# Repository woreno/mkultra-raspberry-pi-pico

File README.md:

# mkultra-raspberry-pi-pico
A stereo audio recorder and ultrasound player using Raspberry Pi Pico made in 2022

I have severe tinitus running my ears, sometimes suddenly i feel my ears popping. For fun i decided to make a device to record my ears. So this consists of a SD Card reader, a small display, piezo speaker, a set of buttons, a dial (rotary encoder), two small electrec microphones, a op-amp circuit for amplification, and a Raspberry Pi Pico to record the sound. After i added a ultrasonic speaker to sweep frequencies. The Raspberry Pi Pico gadget and the microphone amplifier goes into 2 separated boxes. The microphone amplifier can be disconnected from Raspberry Pi Pico box, and connected to a PC line jack for recording audio using the PC software instead.

The small electrec microphones (cushioned) enters one's ears, and goes to microphone amplifier box then to the Raspberry Pi Pico box where the user can control the recording. There's also an option that draws the microphone levels on screen, so the microphones gain can be ajusted thru the potentiometers inside the amplifier box conveniently. 

While recording, the user can save into a file timestamps generated when a button is pressed. In this way the user can take note when some strange tinitus sound appears by just pressing a button, and review later these timestamps along the recorded file.

The system uses fat filesystem, Pico DMA's ADC channels, two cores, and for performance reasons, it records fat clusters sequentially and writes the fat once the records ends, so the SDCard shall only have files created by this system. The sound is recorded stereo with a 12-bit amplitude quantization due to the Raspberry Pi Pico ADC limits, and the rate (samples per second) can be selected from the user interface. From the main menu user can put the ultrasonic speaker playing, sweeping frequencies with the dial (in this setup i used a cheap ultrasonic speaker (2.5€), capable of 36KHz so just a bit above the human ear limit, 20 kHz. 

**About the results**
There was a constant beat probably coming from heart beats, the recording **test.wav**, after noise reduction, and equalizer, feels very ghostly.

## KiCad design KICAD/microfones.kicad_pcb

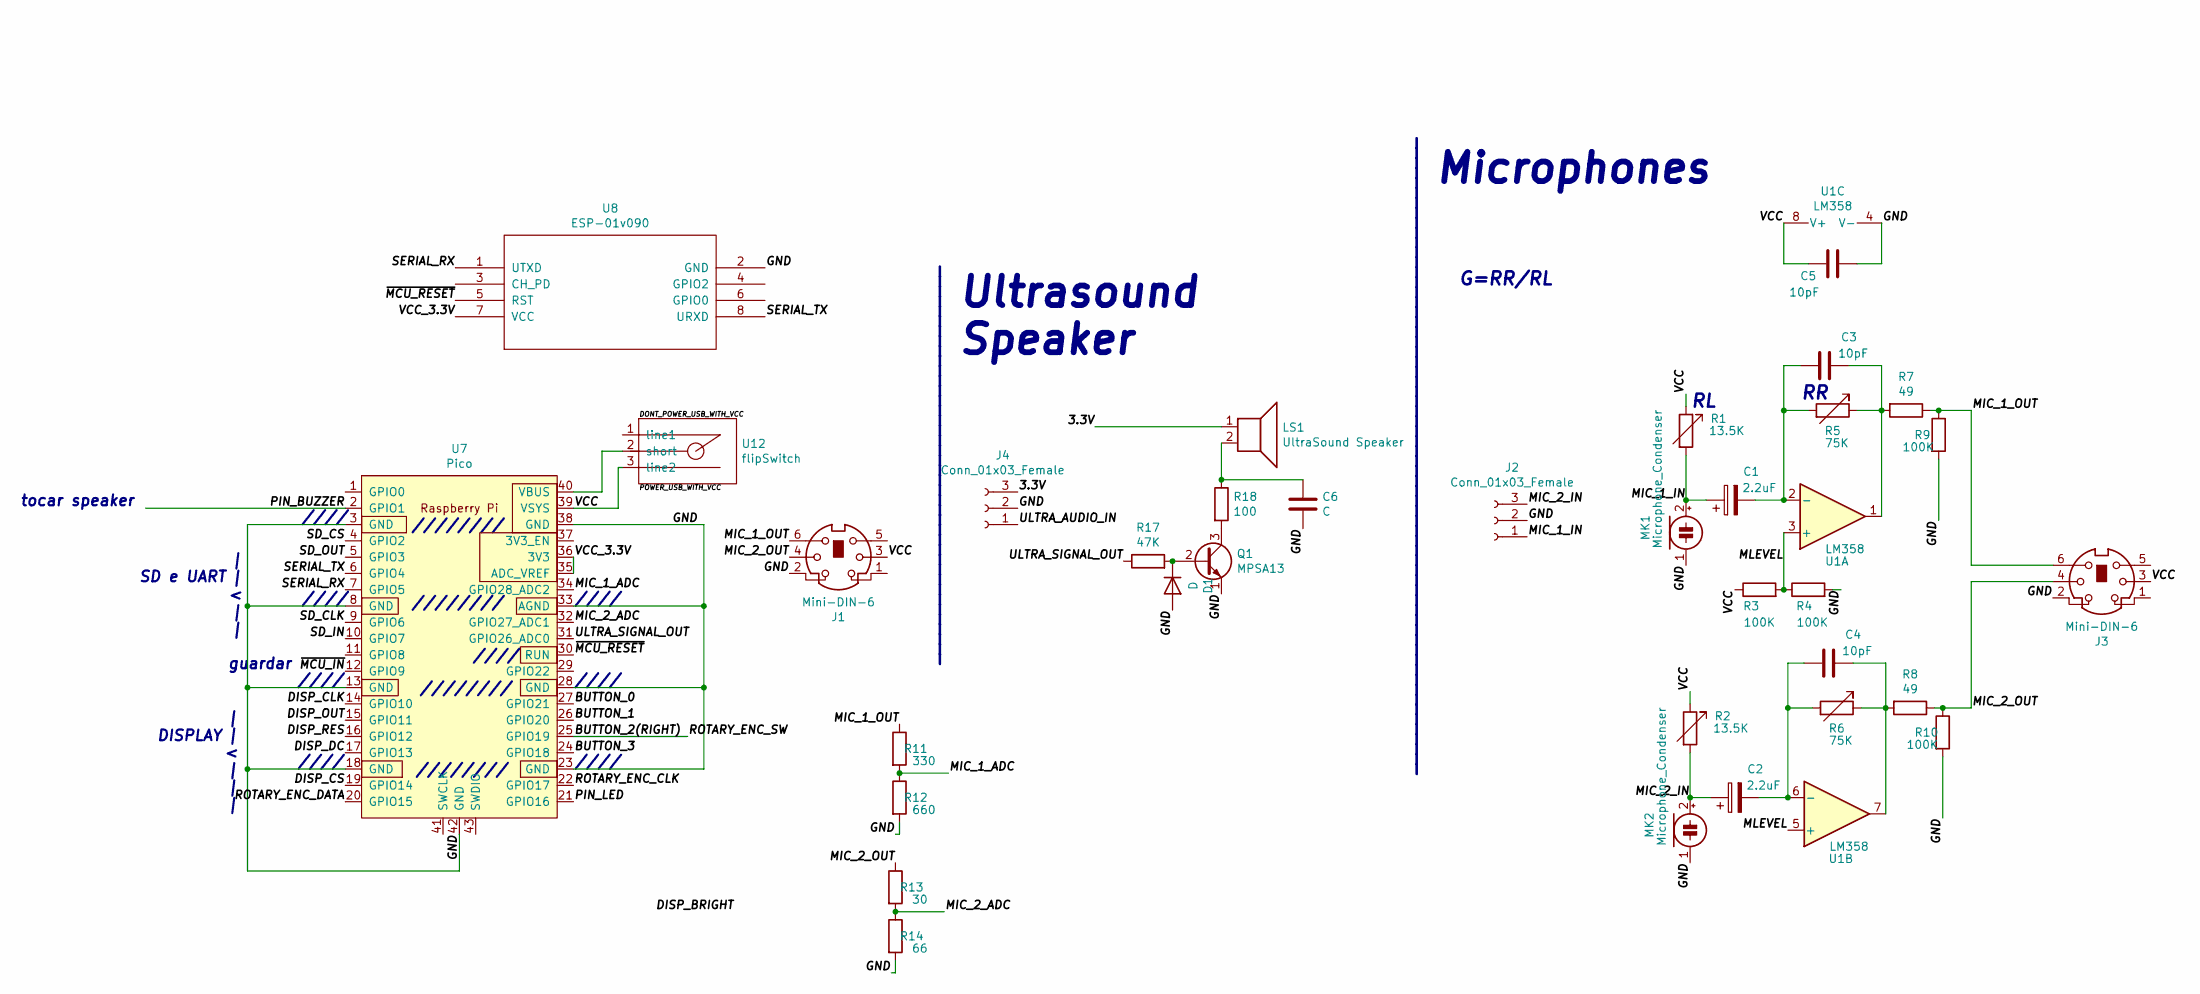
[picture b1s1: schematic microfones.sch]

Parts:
C1, C2: 2.2uF; standard_2pins
C3, C4, C5: 10pF; standard_2pins_half
C6: C; standard_2pins_half
D1: D; standard_2pins
J1, J3: Mini-DIN-6; minidin5
J2, J4: Conn_01x03_Female; PinHeader_1x03_P1.00mm_Horizontal
LS1: UltraSound Speaker; standard_2pins
MK1, MK2: Microphone_Condenser; standard_2pins
Q1: MPSA13; TO-92_Inline
R1, R2: 13.5K; standard_2pins
R3, R4, R9, R10: 100K; standard_2pins
R5, R6: 75K; standard_2pins
R7, R8: 49; standard_2pins
R11: 330; standard_2pins
R12: 660; standard_2pins
R13: 30; standard_2pins
R14: 66; standard_2pins
R17: 47K; standard_2pins
R18: 100; standard_2pins
U1: LM358; standard_DIP_8pins
U7: Pico; RPi_Pico_SMD_TH
U8: ESP-01v090; IDC-Header_2x04_P2.54mm_Horizontal
U12: flipSwitch; flipSwitch3

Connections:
/3.3V: J4.3, LS1.1
/BUTTON_0: U7.27 (GPIO21)
/BUTTON_1: U7.26 (GPIO20)
/BUTTON_2: U7.25 (GPIO19)
/BUTTON_3: U7.24 (GPIO18)
/DISP_CLK: U7.14 (GPIO10)
/DISP_CS: U7.19 (GPIO14)
/DISP_DC: U7.17 (GPIO13)
/DISP_OUT: U7.15 (GPIO11)
/DISP_RES: U7.16 (GPIO12)
/GND: C5.2, C6.2, D1.2 (A), J1.2, J2.2, J3.2, J4.2, MK1.1 (-), MK2.1 (-), Q1.1 (E), R4.2, R9.2, R10.2, R12.2, R14.2, U1.4 (V-), U7.3 (GND), U7.8 (GND), U7.13 (GND), U7.18 (GND), U7.23 (GND), U7.28 (GND), U7.33 (AGND), U7.38 (GND), U7.42 (GND), U8.2 (GND)
/MIC_1_ADC: R11.2, R12.1, U7.34 (GPIO28_ADC2)
/MIC_1_IN: C1.1, J2.1, MK1.2 (+), R1.2
/MIC_1_OUT: J1.6, J3.6, R7.1, R9.1, R11.1
/MIC_2_ADC: R13.2, R14.1, U7.32 (GPIO27_ADC1)
/MIC_2_IN: C2.1, J2.3, MK2.2 (+), R2.2
/MIC_2_OUT: J1.4, J3.4, R8.1, R10.1, R13.1
/MLEVEL: R3.2, R4.1, U1.3 (+), U1.5 (+)
/PIN_BUZZER: U7.2 (GPIO1)
/PIN_LED: U7.21 (GPIO16)
/SD_CLK: U7.9 (GPIO6)
/SD_CS: U7.4 (GPIO2)
/SD_IN: U7.10 (GPIO7)
/SD_OUT: U7.5 (GPIO3)
/SERIAL_RX: U7.7 (GPIO5), U8.1 (UTXD)
/SERIAL_TX: U7.6 (GPIO4), U8.8 (URXD)
/VCC: C5.1, J1.3, J3.3, R1.1, R2.1, R3.1, U1.8 (V+), U7.39 (VSYS), U12.3 (line2)
/VCC_3.3V: U7.35 (ADC_VREF), U7.36 (3V3), U8.7 (VCC)
/~MCU_IN: U7.12 (GPIO9)
/~MCU_RESET: U7.30 (RUN), U8.5 (RST)
unnamed: C1.2, C3.2, R5.2, U1.2 (-)
unnamed: C2.2, C4.2, R6.2, U1.6 (-)
unnamed: C3.1, R5.1, R7.2, U1.1
unnamed: C4.1, R6.1, R8.2, U1.7
unnamed: C6.1, LS1.2, R18.1
unnamed: D1.1 (K), Q1.2 (B), R17.2
unnamed: Q1.3 (C), R18.2
unnamed: U7.40 (VBUS), U12.2 (short)

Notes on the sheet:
| | < | |
SD e UART
| | < | | |
DISPLAY
////
////////
guardar
tocar speaker
Ultrasound Speaker
________________________________________
________________________________________________________________
Microphones
G=RR/RL

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
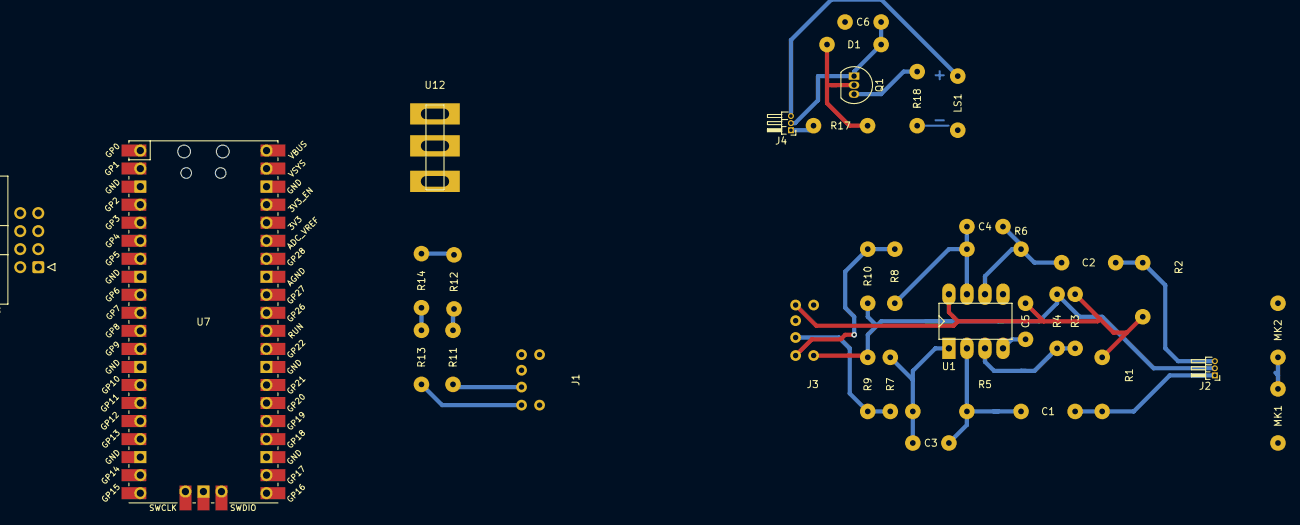
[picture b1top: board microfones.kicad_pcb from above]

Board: 2 copper layers, 35 parts (0 on the bottom side), 23 nets.
